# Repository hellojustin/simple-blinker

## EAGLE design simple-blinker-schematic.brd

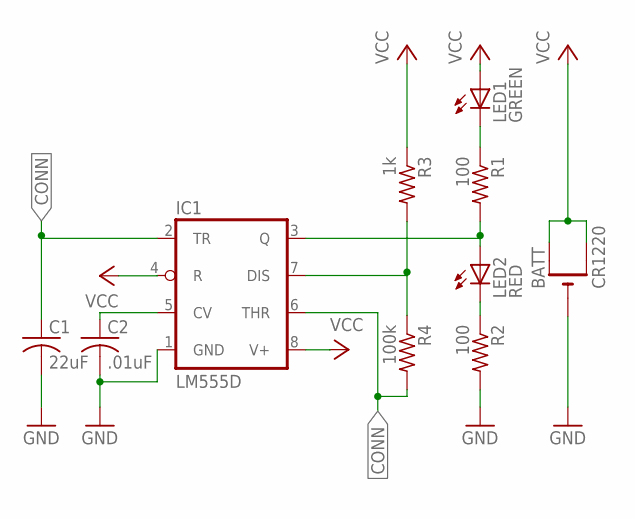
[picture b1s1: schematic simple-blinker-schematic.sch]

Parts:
BATT: CR1220; CR1220-SMD
C1: 22uF; C0805; MPN 293D226X9016B2TE3
C2: .01uF; C0805; MPN SR211C103KAA.
IC1: LM555D; SO08
LED1: GREEN; CHIPLED_0805
LED2: RED; CHIPLED_0805
R1, R2: 100; R0805; MPN CRCW1206100RFKTA
R3: 1k; R0805; MPN CRCW08051K00FKEB
R4: 100k; R0805; MPN TNPW0805100KBEEA

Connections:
CONN: C1.1, IC1.2 (TR), IC1.6 (THR), R4.2
GND: BATT.-, C1.2, C2.2, IC1.1 (GND), R2.2
unnamed: LED1.C, R1.1
unnamed: IC1.3 (Q), LED2.A, R1.2
unnamed: LED2.C, R2.1
unnamed: IC1.7 (DIS), R3.2, R4.1
unnamed: C2.1, IC1.5 (CV)
VCC: BATT.+$1 (+), BATT.+$2 (+1), IC1.4 (R), IC1.8 (V+), LED1.A, R3.1

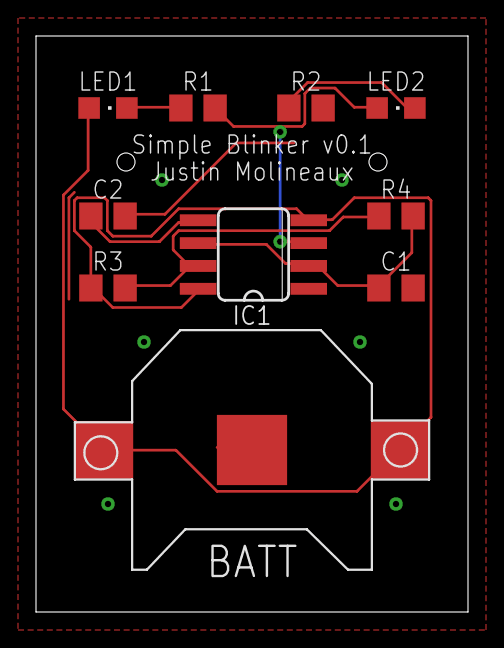
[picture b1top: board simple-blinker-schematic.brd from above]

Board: 2 copper layers, 24.0 x 32.0 mm, 10 parts (0 on the bottom side), 8 nets.

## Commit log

2018-12-15 Initial commit.
2018-12-22 Update eagle file, remove/ignore .DS_Store.
